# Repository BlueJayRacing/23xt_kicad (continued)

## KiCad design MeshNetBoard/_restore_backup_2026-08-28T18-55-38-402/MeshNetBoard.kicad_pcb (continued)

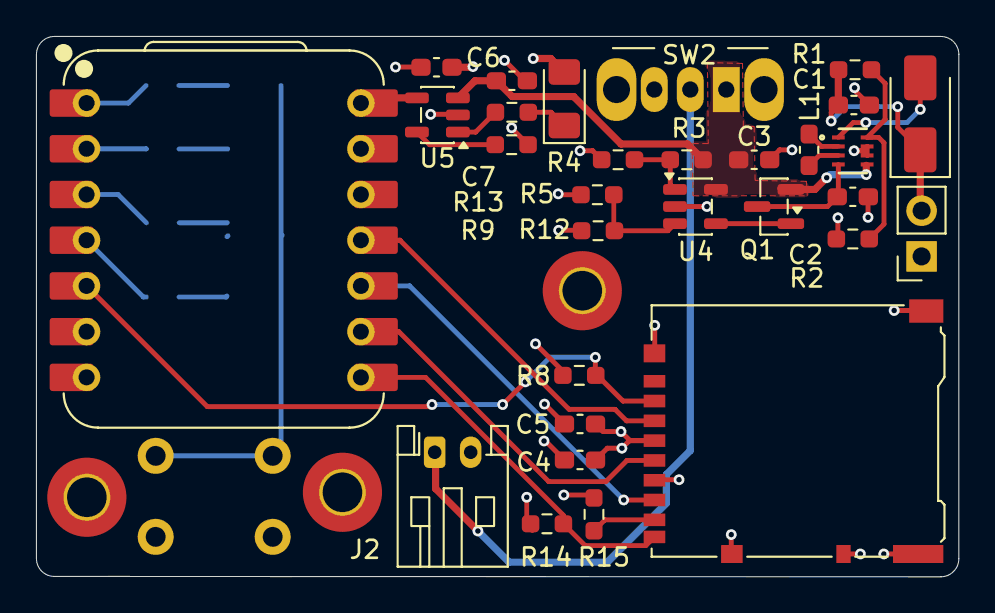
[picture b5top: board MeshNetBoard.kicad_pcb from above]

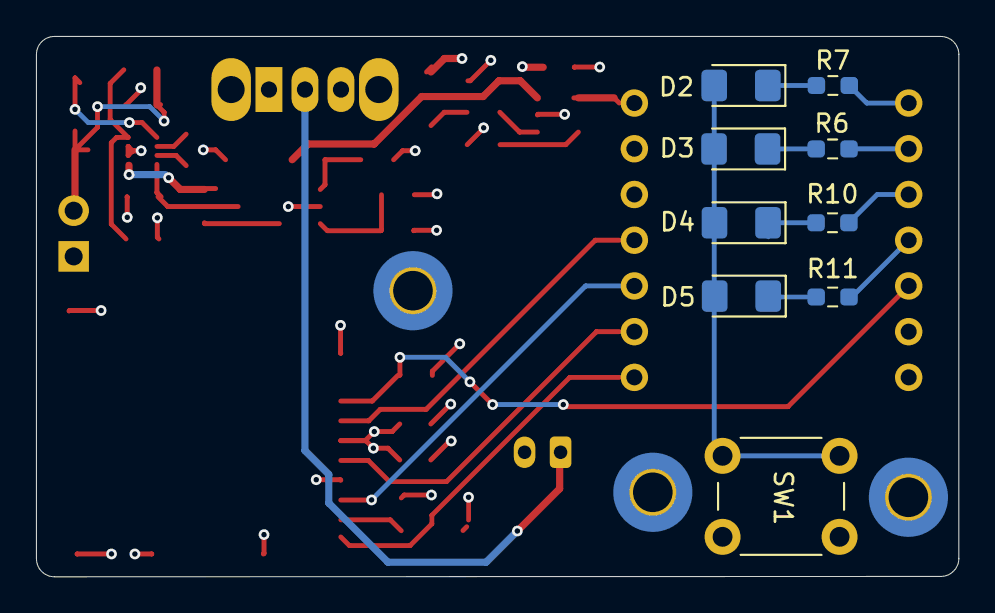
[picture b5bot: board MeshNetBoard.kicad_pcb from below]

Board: 4 copper layers, 51.2 x 30.0 mm, 42 parts (9 on the bottom side), 32 nets.

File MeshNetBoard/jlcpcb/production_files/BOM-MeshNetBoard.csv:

Comment,Designator,Footprint,LCSC,Quantity
0.1μF,C3,C_0603_1608Metric_Pad1.08x0.95mm_HandSolder,C125205,1
1.74M,R3,R_0603_1608Metric_Pad0.98x0.95mm_HandSolder,C422975,1
100nF,C4,C_0603_1608Metric_Pad1.08x0.95mm_HandSolder,C14663,1
10k,"R14,R15,R8",R_0603_1608Metric_Pad0.98x0.95mm_HandSolder,C23192,3
10µF,C5,C_0603_1608Metric_Pad1.08x0.95mm_HandSolder,C19702,1
1M,"R12,R4",R_0603_1608Metric_Pad0.98x0.95mm_HandSolder,C22935,2
1µH,L1,L_0603_1608Metric_Pad1.05x0.95mm_HandSolder,C98326,1
22µF,C2,C_0603_1608Metric_Pad1.08x0.95mm_HandSolder,C59461,1
2M,R5,R_0603_1608Metric_Pad0.98x0.95mm_HandSolder,C22976,1
2k,R9,R_0603_1608Metric_Pad0.98x0.95mm_HandSolder,C22975,1
330,"R10,R11,R6,R7",R_0603_1608Metric_Pad0.98x0.95mm_HandSolder,C23138,4
4.7µF,"C6,C7",C_0603_1608Metric_Pad1.08x0.95mm_HandSolder,C19666,2
470,R13,R_0603_1608Metric_Pad0.98x0.95mm_HandSolder,C23179,1
47µF,C1,C_0603_1608Metric_Pad1.08x0.95mm_HandSolder,C140782,1
511k,R1,R_0603_1608Metric_Pad0.98x0.95mm_HandSolder,C23194,1
91k,R2,R_0603_1608Metric_Pad0.98x0.95mm_HandSolder,C23265,1
Conn_01x02,J2,JST_PH_S2B-PH-K_1x02_P2.00mm_Horizontal,C173752,1
Jumper_2_Open,JP1,PinSocket_1x02_P2.54mm_Vertical,C6823945,1
LED,"D2,D3,D4,D5,D6",LED_1206_3216Metric_Pad1.42x1.75mm_HandSolder,C2827254,5
MAX9031AU,U4,SOT-23-5,C117531,1
MCP73831-2-OT,U5,SOT-23-5,C424093,1
Micro_SD_Card_Det_Hirose_DM3AT,J3,microSD_HC_Hirose_DM3AT-SF-PEJM5,C114218,1
Q_PMOS_GSD,Q1,SOT-23,C10487,1
SS14,D1,D_SMA,C2480,1
SW_Push,SW1,SW_PUSH_6mm_H5mm,C428628,1
SW_SPST,SW2,SW_Slide_SPDT_Angled_CK_OS102011MA1Q,C19192981,1
TPS631000DRLR,U2,TPS631000DRLR_TEX,C5219190,1
XIAO-ESP32-S3-DIP,U1,XIAO-ESP32-S3-DIP,C48405120,1

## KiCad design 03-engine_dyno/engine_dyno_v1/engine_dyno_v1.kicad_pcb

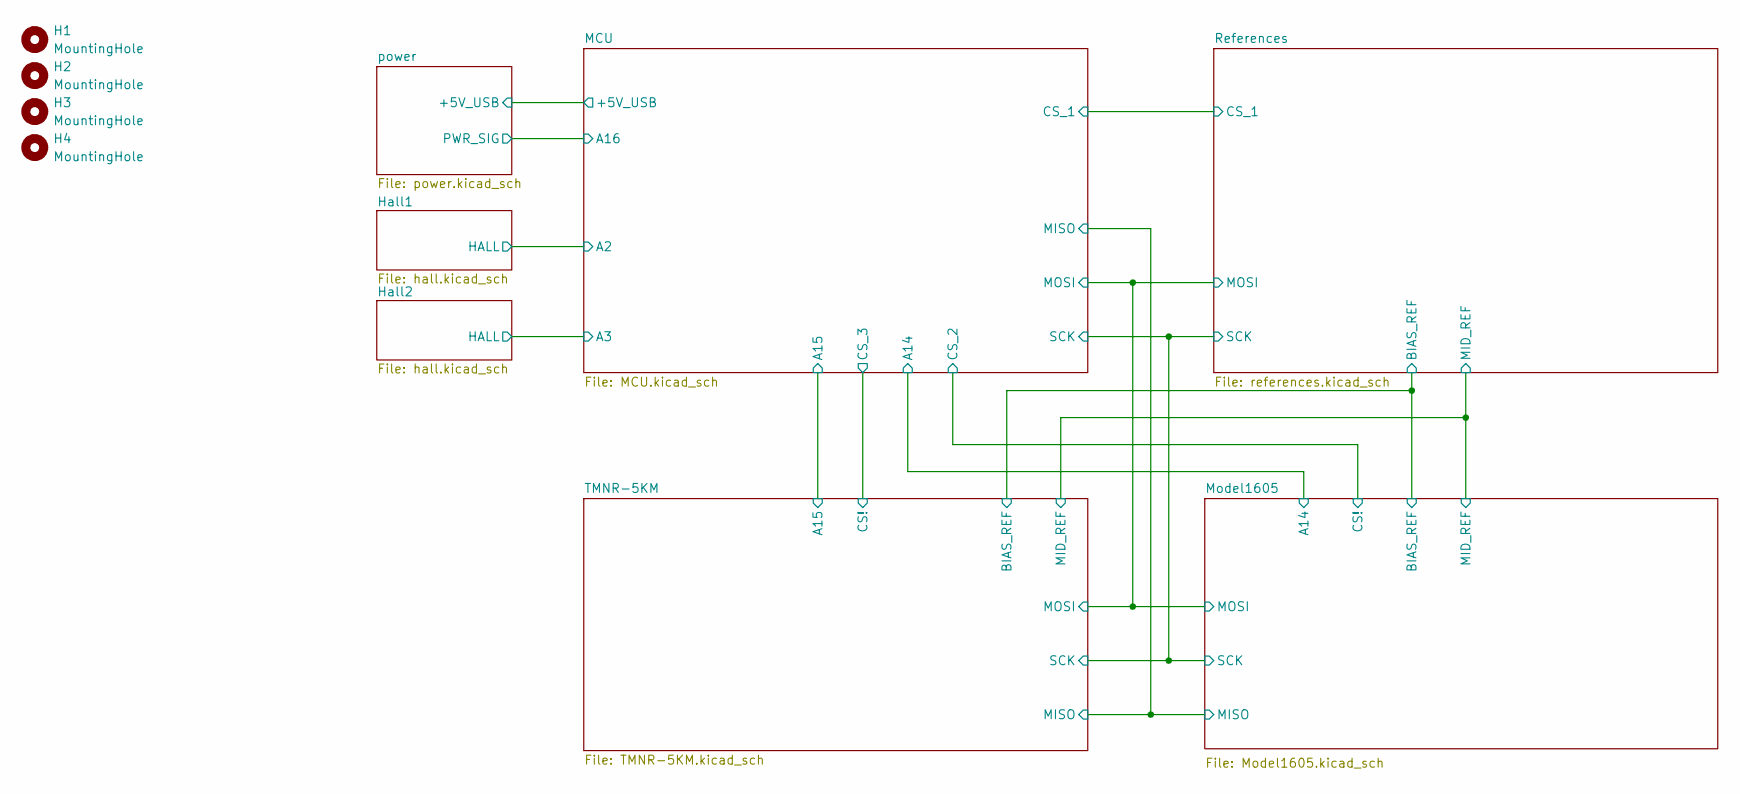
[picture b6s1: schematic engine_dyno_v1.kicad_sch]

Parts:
H1, H2, H3, H4: MountingHole; MountingHole_3.2mm_M3_DIN965_Pad

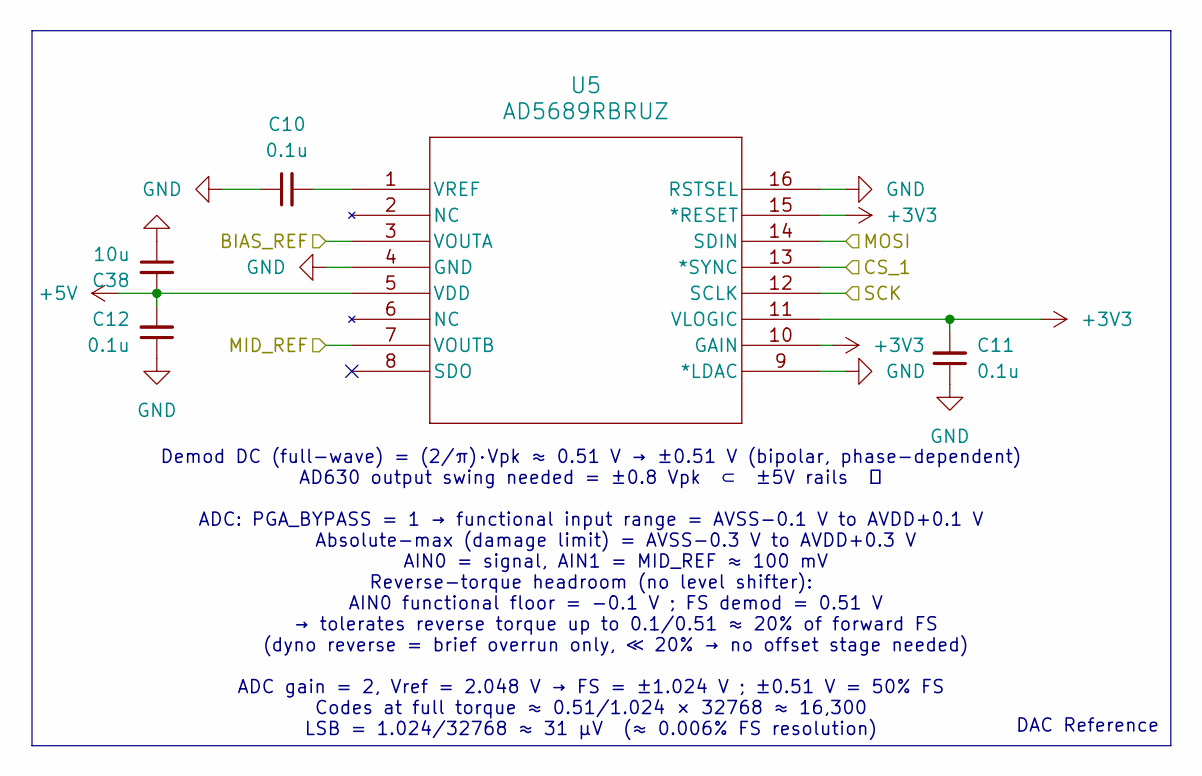
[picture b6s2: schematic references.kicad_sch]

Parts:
C10, C11, C12: 0.1u; C_0402_1005Metric
C38: 10u; C_0402_1005Metric
U5: AD5689RBRUZ; RU_16_ADI

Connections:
+3V3: C11.2, U5.10 (GAIN), U5.11 (VLOGIC), U5.15 (*RESET); also elsewhere on the board
+5V: C12.2, C38.2, U5.5 (VDD); also elsewhere on the board
/MCU/CS_1: U5.13 (*SYNC); also elsewhere on the board
/MCU/MOSI: U5.14 (SDIN); also elsewhere on the board
/MCU/SCK: U5.12 (SCLK); also elsewhere on the board
/Model1605/BIAS_REF: U5.3 (VOUTA); also elsewhere on the board
/Model1605/MID_REF: U5.7 (VOUTB); also elsewhere on the board
GND: C10.1, C11.1, C12.1, C38.1, U5.4 (GND), U5.9 (*LDAC), U5.16 (RSTSEL); also elsewhere on the board
unnamed: C10.2, U5.1 (VREF)

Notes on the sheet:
Demod DC (full-wave) = (2/π)·Vpk ≈ 0.51 V → ±0.51 V (bipolar, phase-dependent) AD630 output swing needed = ±0.8 Vpk ⊂ ±5V rails ✓ ADC: PGA_BYPASS = 1 → functional input range = AVSS−0.1 V to AVDD+0.1 V Absolute-max (damage limit) = AVSS−0.3 V to AVDD+0.3 V AIN0 = signal, AIN1 = MID_REF ≈ 100 mV Rev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
DAC Reference

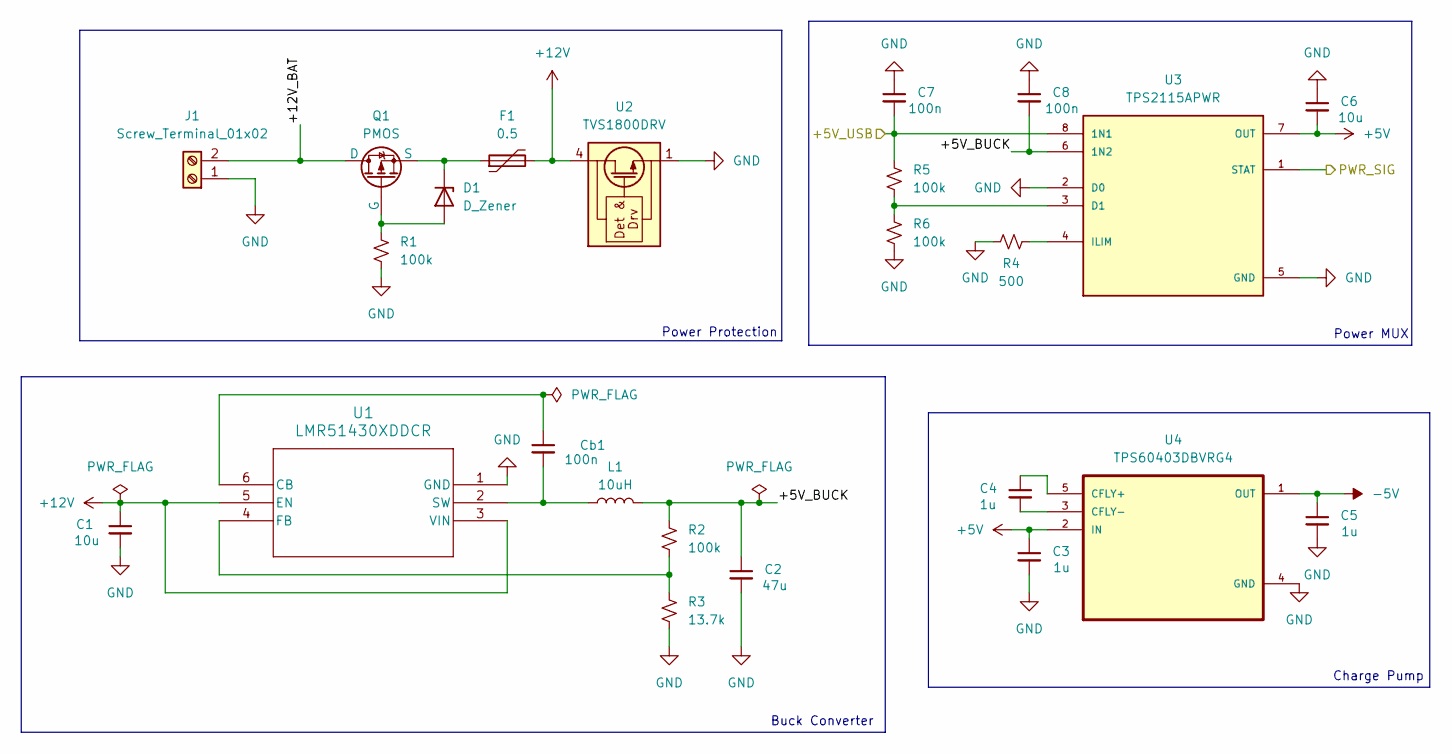
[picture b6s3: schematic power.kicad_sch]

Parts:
C1, C6: 10u; C_0402_1005Metric
C2: 47u; C_0402_1005Metric
C3, C4, C5: 1u; C_0402_1005Metric
C7, C8: 100n; C_0402_1005Metric
Cb1: 100n; C_0402_1005Metric
D1: D_Zener; D_SOD-123F
F1: 0.5; 0ZCH0050FF2G
J1: Screw_Terminal_01x02; TerminalBlock_RND_205-00232_1x02_P5.08mm_Horizontal
L1: 10uH; WE-MAPI_3020; MPN 74438336100
Q1: PMOS; SOT-23-3
R1, R2, R5, R6: 100k; R_0402_1005Metric
R3: 13.7k; R_0402_1005Metric
R4: 500; R_0402_1005Metric
U1: LMR51430XDDCR; SOT-23-THIN-6_DDC_TEX
U2: TVS1800DRV; WSON-6-1EP_2x2mm_P0.65mm_EP1x1.6mm
U3: TPS2115APWR; SOP65P640X120-8N; PARTREV F
U4: TPS60403DBVRG4; SOT95P280X145-5N

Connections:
+5V: C3.1, C6.2, U3.7 (OUT), U4.2 (IN); also elsewhere on the board
+12V: C1.1, F1.2, U1.3 (VIN), U1.5 (EN), U2.4 (IN), U2.5 (IN), U2.6 (IN)
-5V: C5.1, U4.1 (OUT); also elsewhere on the board
/MCU/+5V_USB: C7.2, R5.2, U3.8 (1N1); also elsewhere on the board
/MCU/A16: U3.1 (STAT); also elsewhere on the board
/power/+5V_BUCK: C2.1, C8.2, L1.2, R2.1, U3.6 (1N2)
/power/+12V_BAT: J1.2, Q1.1 (D)
GND: C1.2, C2.2, C3.2, C5.2, C6.1, C7.1, C8.1, J1.1, R1.2, R3.2, R4.2, R6.1, U1.1 (GND), U2.1 (GND), U2.2 (GND), U2.3 (GND), U2.7 (GND), U3.2 (D0), U3.5 (GND), U4.4 (GND); also elsewhere on the board
unnamed: D1.2 (A), Q1.2 (G), R1.1
unnamed: D1.1 (K), F1.1, Q1.3 (S)
unnamed: Cb1.1, U1.6 (CB)
unnamed: R2.2, R3.1, U1.4 (FB)
unnamed: Cb1.2, L1.1, U1.2 (SW)
unnamed: R5.1, R6.2, U3.3 (D1)
unnamed: R4.1, U3.4 (ILIM)
unnamed: C4.1, U4.5 (CFLY+)
unnamed: C4.2, U4.3 (CFLY-)

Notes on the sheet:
Power MUX
Charge Pump
Buck Converter
Power Protection

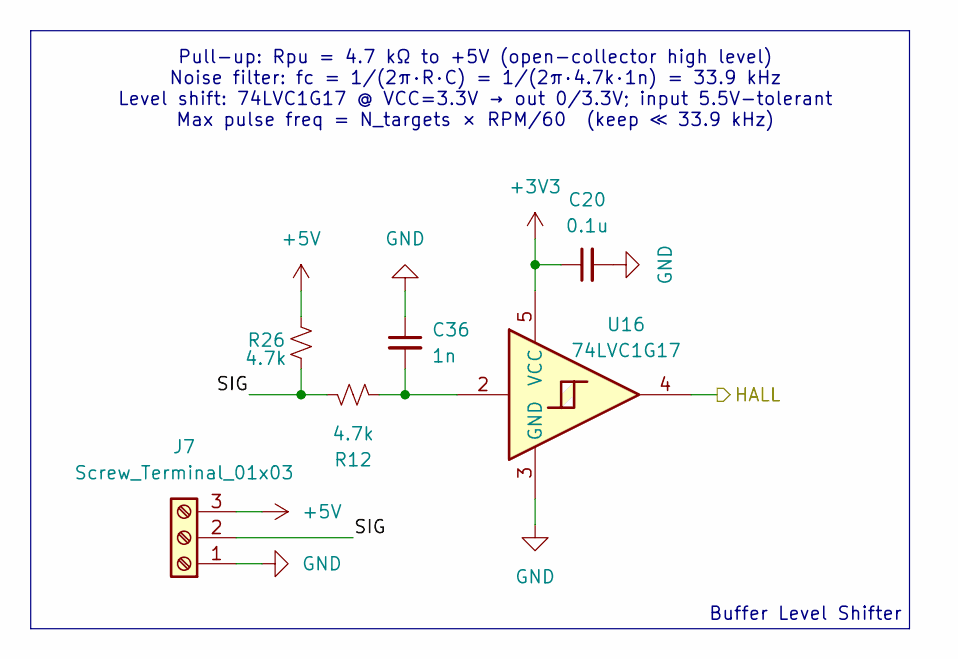
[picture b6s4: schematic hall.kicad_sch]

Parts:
C20: 0.1u; C_0402_1005Metric
C36: 1n; C_0402_1005Metric
J7: Screw_Terminal_01x03; TerminalBlock_RND_205-00233_1x03_P5.08mm_Horizontal
R12, R26: 4.7k; R_0402_1005Metric
U16: 74LVC1G17; SOT-23-5

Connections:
+3V3: C20.1, U16.5 (VCC); also elsewhere on the board
+5V: J7.3, R26.1; also elsewhere on the board
/Hall1/HALL: U16.4; also elsewhere on the board
/Hall1/SIG: J7.2, R12.1, R26.2
GND: C20.2, C36.1, J7.1, U16.3 (GND); also elsewhere on the board
unnamed: C36.2, R12.2, U16.2

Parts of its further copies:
C25: 0.1u; C_0402_1005Metric
C26: 1n; C_0402_1005Metric
J5: Screw_Terminal_01x03; TerminalBlock_RND_205-00233_1x03_P5.08mm_Horizontal
R17, R18: 4.7k; R_0402_1005Metric
U11: 74LVC1G17; SOT-23-5

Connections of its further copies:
+3V3: C25.1, U11.5 (VCC); also elsewhere on the board
+5V: J5.3, R17.1; also elsewhere on the board
/Hall2/HALL: U11.4; also elsewhere on the board
/Hall2/SIG: J5.2, R17.2, R18.1
GND: C25.2, C26.1, J5.1, U11.3 (GND); also elsewhere on the board
unnamed: C26.2, R18.2, U11.2

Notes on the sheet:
Pull-up: Rpu = 4.7 kΩ to +5V (open-collector high level) Noise filter: fc = 1/(2π·R·C) = 1/(2π·4.7k·1n) = 33.9 kHz Level shift: 74LVC1G17 @ VCC=3.3V → out 0/3.3V; input 5.5V-tolerant Max pulse freq = N_targets × RPM/60 (keep ≪ 33.9 kHz)
Buffer Level Shifter

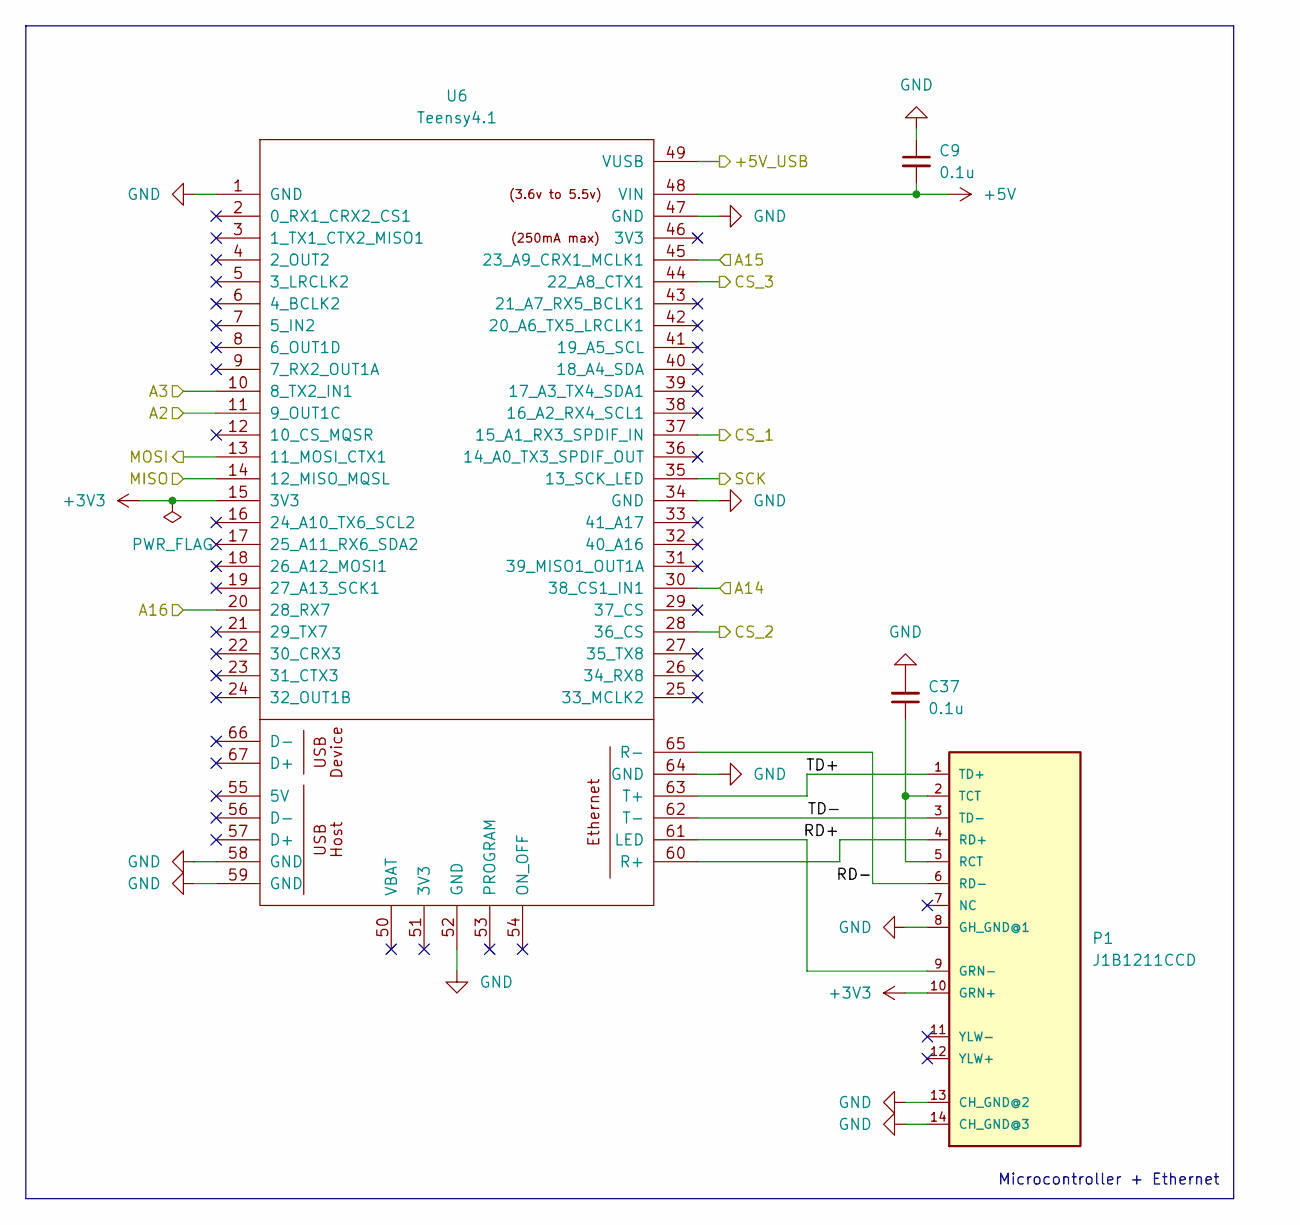
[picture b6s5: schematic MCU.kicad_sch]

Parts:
C9, C37: 0.1u; C_0402_1005Metric
P1: J1B1211CCD
U6: Teensy4.1; Teensy41

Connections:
+3V3: P1.10 (GRN+), U6.15 (3V3); also elsewhere on the board
+5V: C9.2, U6.48 (VIN); also elsewhere on the board
/Hall1/HALL: U6.11 (9_OUT1C); also elsewhere on the board
/Hall2/HALL: U6.10 (8_TX2_IN1); also elsewhere on the board
/MCU/+5V_USB: U6.49 (VUSB); also elsewhere on the board
/MCU/A14: U6.30 (38_CS1_IN1); also elsewhere on the board
/MCU/A15: U6.45 (23_A9_CRX1_MCLK1); also elsewhere on the board
/MCU/A16: U6.20 (28_RX7); also elsewhere on the board
/MCU/CS_1: U6.37 (15_A1_RX3_SPDIF_IN); also elsewhere on the board
/MCU/CS_2: U6.28 (36_CS); also elsewhere on the board
/MCU/CS_3: U6.44 (22_A8_CTX1); also elsewhere on the board
/MCU/MISO: U6.14 (12_MISO_MQSL); also elsewhere on the board
/MCU/MOSI: U6.13 (11_MOSI_CTX1); also elsewhere on the board
/MCU/RD+: P1.4 (RD+), U6.60 (R+)
/MCU/RD-: P1.6 (RD-), U6.65 (R-)
/MCU/SCK: U6.35 (13_SCK_LED); also elsewhere on the board
/MCU/TD+: P1.1 (TD+), U6.63 (T+)
/MCU/TD-: P1.3 (TD-), U6.62 (T-)
GND: C9.1, C37.2, P1.8 (GH_GND@1), P1.13 (CH_GND@2), P1.14 (CH_GND@3), U6.1 (GND), U6.34 (GND), U6.47 (GND), U6.52 (GND), U6.58 (GND), U6.59 (GND), U6.64 (GND); also elsewhere on the board
unnamed: P1.9 (GRN-), U6.61 (LED)
unnamed: C37.1, P1.2 (TCT), P1.5 (RCT)

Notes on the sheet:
Microcontroller + Ethernet

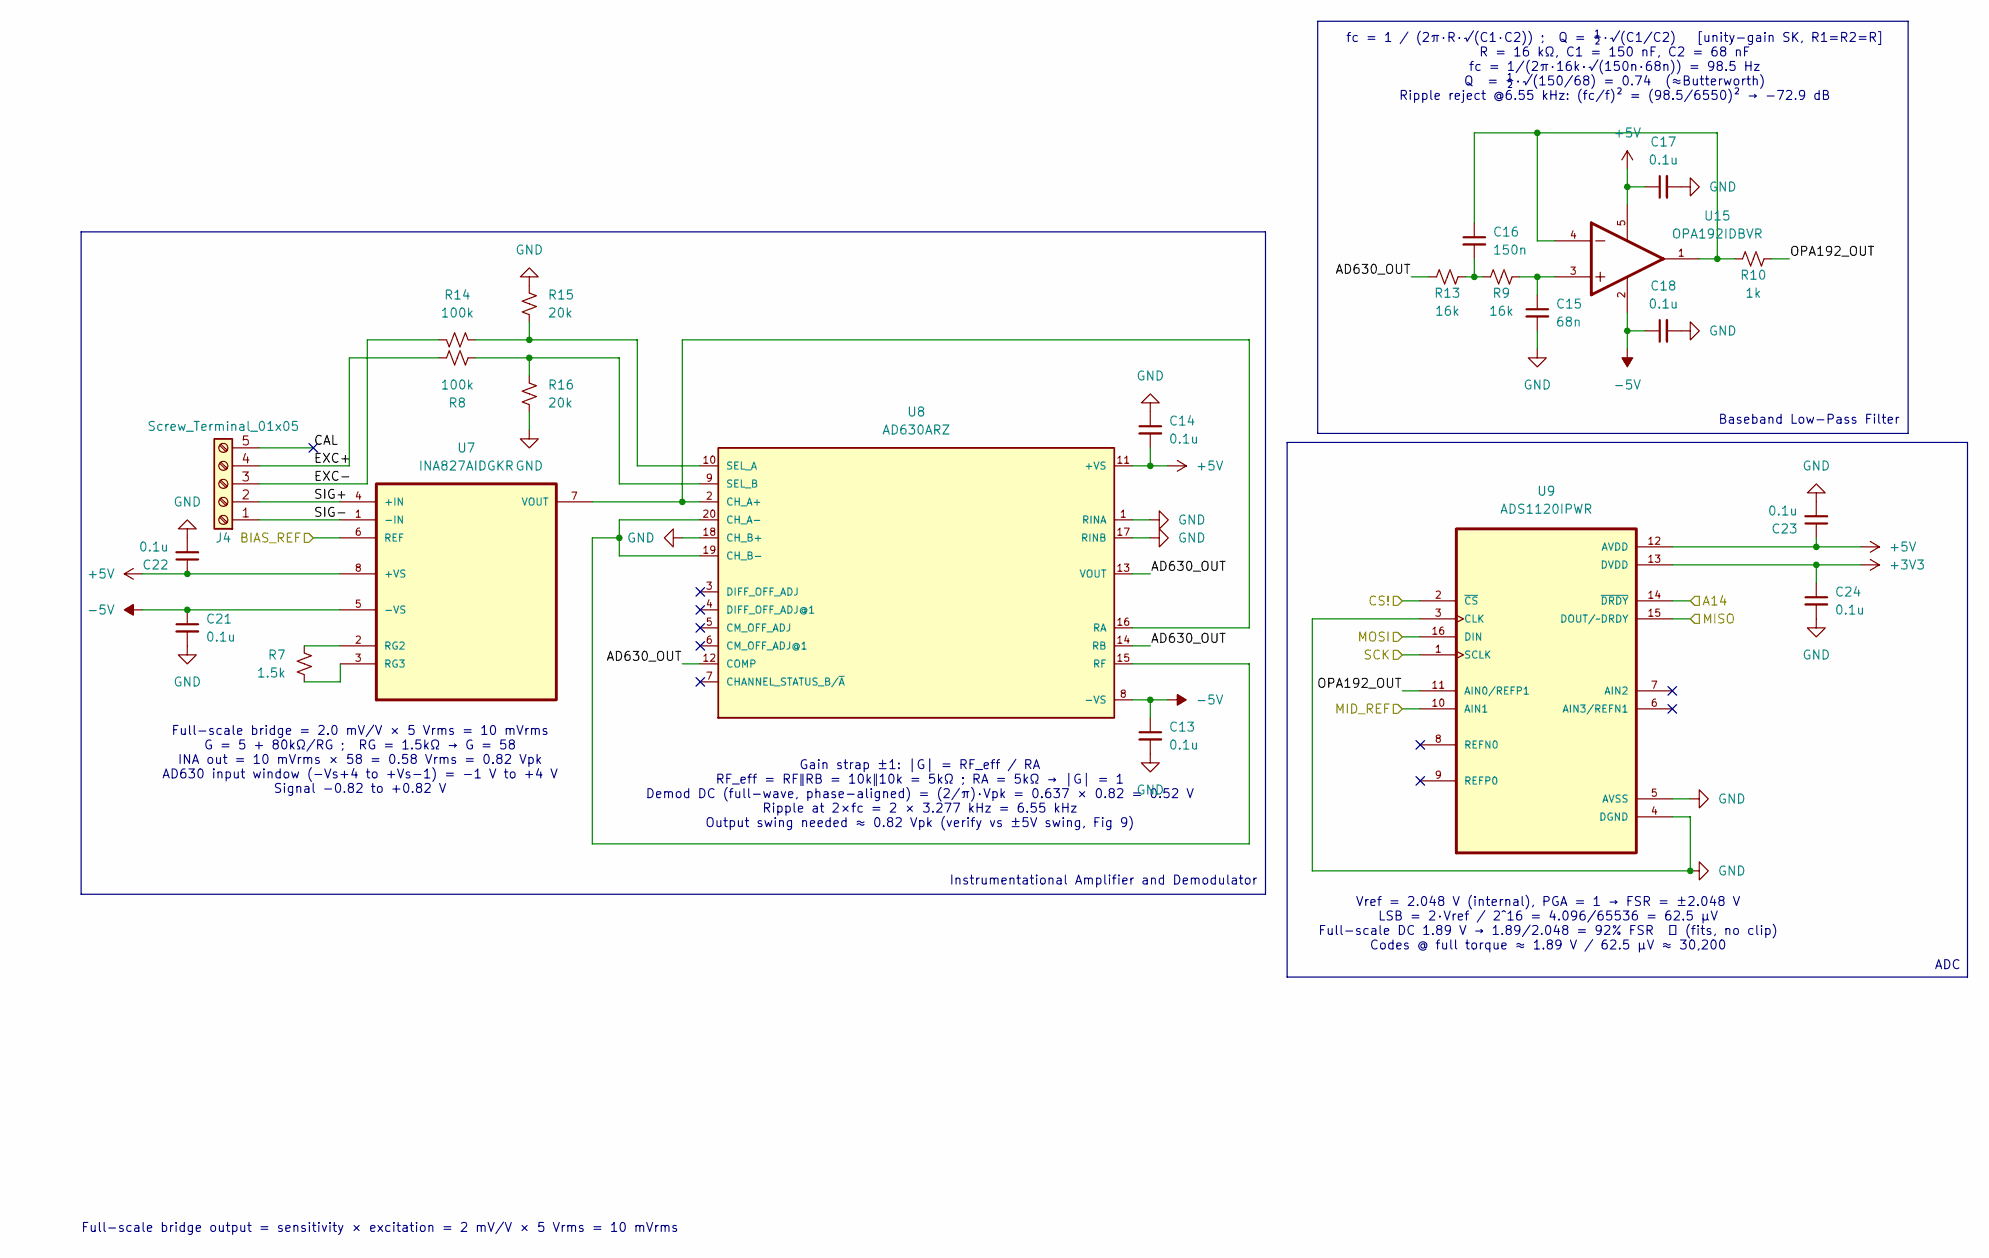
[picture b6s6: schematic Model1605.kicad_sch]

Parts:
C13, C14, C17, C18, C21, C22, C23, C24: 0.1u; C_0402_1005Metric
C15: 68n; C_0402_1005Metric
C16: 150n; C_0402_1005Metric
J4: Screw_Terminal_01x05; TerminalBlock_RND_205-00235_1x05_P5.08mm_Horizontal
R7: 1.5k; R_0402_1005Metric
R8, R14: 100k; R_0402_1005Metric
R9, R13: 16k; R_0402_1005Metric
R10: 1k; R_0402_1005Metric
R15, R16: 20k; R_0402_1005Metric
U7: INA827AIDGKR; SOP65P490X110-8N; DigiKey_Part_Number 296-30588-1-ND
U8: AD630ARZ; SOIC127P1032X265-20N
U9: ADS1120IPWR; SOP65P640X120-16N
U15: OPA192IDBVR; SOT95P280X145-5N; PARTREV F

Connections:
+3V3: C24.1, U9.13 (DVDD); also elsewhere on the board
+5V: C14.2, C17.1, C22.1, C23.1, U7.8 (+VS), U8.11 (+VS), U9.12 (AVDD), U15.5; also elsewhere on the board
-5V: C13.1, C18.1, C21.1, U7.5 (-VS), U8.8 (-VS), U15.2; also elsewhere on the board
/MCU/A14: U9.14 (~DRDY); also elsewhere on the board
/MCU/CS_2: U9.2 (~CS); also elsewhere on the board
/MCU/MISO: U9.15 (DOUT/~DRDY); also elsewhere on the board
/MCU/MOSI: U9.16 (DIN); also elsewhere on the board
/MCU/SCK: U9.1 (SCLK); also elsewhere on the board
/Model1605/AD630_OUT: R13.1, U8.12 (COMP), U8.13 (VOUT), U8.14 (RB)
/Model1605/BIAS_REF: U7.6 (REF); also elsewhere on the board
/Model1605/CAL: J4.5
/Model1605/EXC+: J4.4, R8.1
/Model1605/EXC-: J4.3, R14.1
/Model1605/MID_REF: U9.10 (AIN1); also elsewhere on the board
/Model1605/OPA192_OUT: R10.2, U9.11 (AIN0/REFP1)
/Model1605/SIG+: J4.2, U7.4 (+IN)
/Model1605/SIG-: J4.1, U7.1 (-IN)
GND: C13.2, C14.1, C15.2, C17.2, C18.2, C21.2, C22.2, C23.2, C24.2, R15.2, R16.1, U8.1 (RINA), U8.17 (RINB), U8.18 (CH_B+), U9.3 (CLK), U9.4 (DGND), U9.5 (AVSS); also elsewhere on the board
unnamed: C15.1, R9.2, U15.3
unnamed: C16.1, R10.1, U15.1, U15.4
unnamed: C16.2, R9.1, R13.2
unnamed: R7.1, U7.2 (RG2)
unnamed: R7.2, U7.3 (RG3)
unnamed: U7.7 (VOUT), U8.2 (CH_A+), U8.16 (RA)
unnamed: U8.15 (RF), U8.19 (CH_B-), U8.20 (CH_A-)
unnamed: R14.2, R15.1, U8.10 (SEL_A)
unnamed: R8.2, R16.2, U8.9 (SEL_B)

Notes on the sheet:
Baseband Low-Pass Filter
Vref = 2.048 V (internal), PGA = 1 → FSR = ±2.048 V LSB = 2·Vref / 2^16 = 4.096/65536 = 62.5 µV Full-scale DC 1.89 V → 1.89/2.048 = 92% FSR ✓ (fits, no clip) Codes @ full torque ≈ 1.89 V / 62.5 µV ≈ 30,200
Full-scale bridge = 2.0 mV/V × 5 Vrms = 10 mVrms G = 5 + 80kΩ/RG ; RG = 1.5kΩ → G = 58 INA out = 10 mVrms × 58 = 0.58 Vrms = 0.82 Vpk AD630 input window (−Vs+4 to +Vs−1) = −1 V to +4 V Signal −0.82 to +0.82 V
Full-scale bridge output = sensitivity × excitation = 2 mV/V × 5 Vrms = 10 mVrms
fc = 1 / (2π·R·√(C1·C2)) ; Q = ½·√(C1/C2) [unity-gain SK, R1=R2=R] R = 16 kΩ, C1 = 150 nF, C2 = 68 nF fc = 1/(2π·16k·√(150n·68n)) = 98.5 Hz Q = ½·√(150/68) = 0.74 (≈Butterworth) Ripple reject @6.55 kHz: (fc/f)² = (98.5/6550)² → −72.9 dB
Instrumentational Amplifier and Demodulator
ADC
Gain strap ±1: |G| = RF_eff / RA RF_eff = RF‖RB = 10k‖10k = 5kΩ ; RA = 5kΩ → |G| = 1 Demod DC (full-wave, phase-aligned) = (2/π)·Vpk = 0.637 × 0.82 = 0.52 V Ripple at 2×fc = 2 × 3.277 kHz = 6.55 kHz Output swing needed ≈ 0.82 Vpk (verify vs ±5V swing, Fig 9)

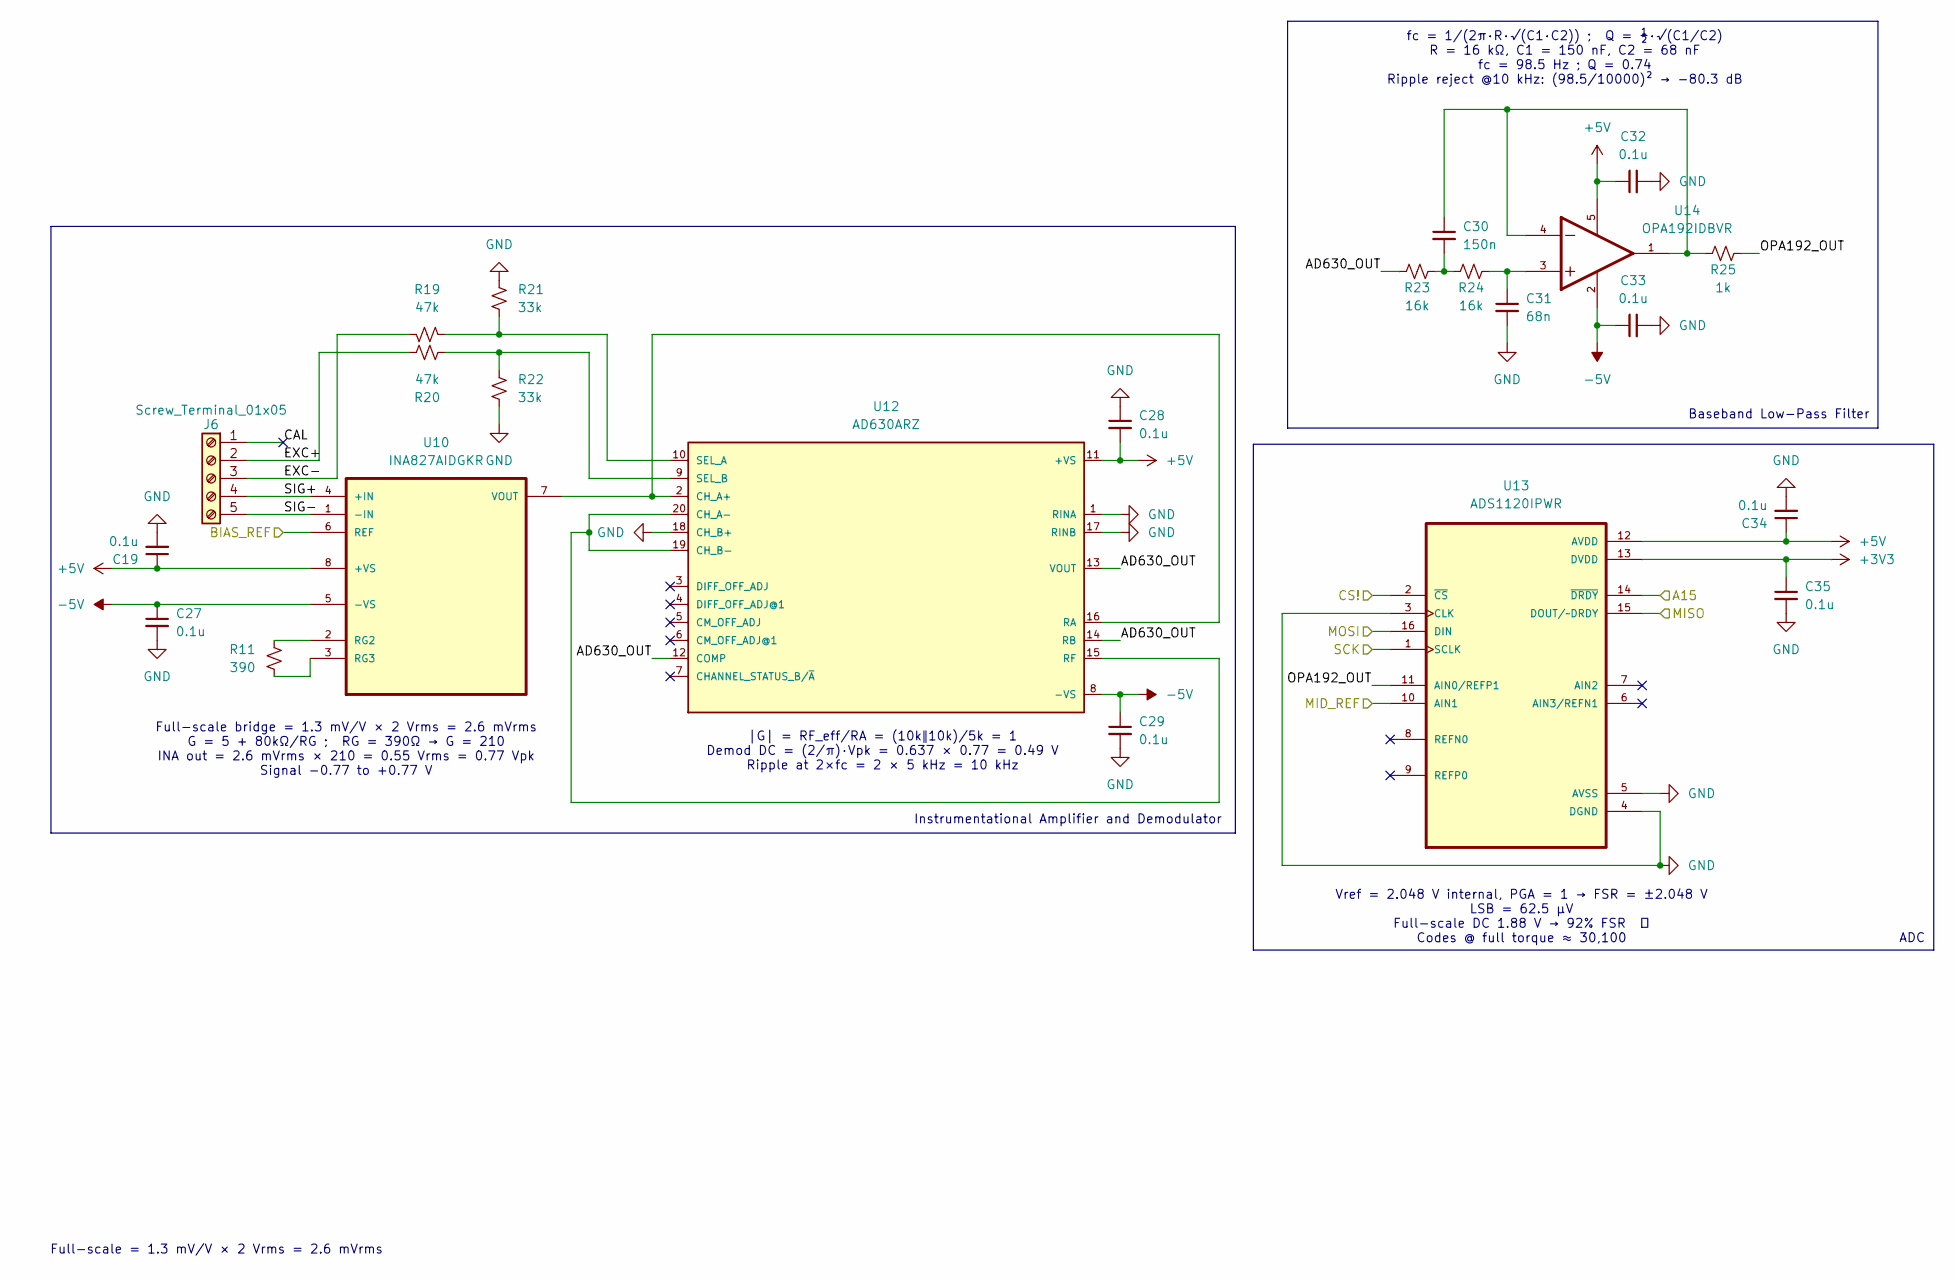
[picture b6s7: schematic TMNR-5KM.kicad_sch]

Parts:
C19, C27, C28, C29, C32, C33, C34, C35: 0.1u; C_0402_1005Metric
C30: 150n; C_0402_1005Metric
C31: 68n; C_0402_1005Metric
J6: Screw_Terminal_01x05; TerminalBlock_RND_205-00235_1x05_P5.08mm_Horizontal
R11: 390; R_0402_1005Metric
R19, R20: 47k; R_0402_1005Metric
R21, R22: 33k; R_0402_1005Metric
R23, R24: 16k; R_0402_1005Metric
R25: 1k; R_0402_1005Metric
U10: INA827AIDGKR; SOP65P490X110-8N; DigiKey_Part_Number 296-30588-1-ND
U12: AD630ARZ; SOIC127P1032X265-20N
U13: ADS1120IPWR; SOP65P640X120-16N
U14: OPA192IDBVR; SOT95P280X145-5N; PARTREV F

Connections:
+3V3: C35.1, U13.13 (DVDD); also elsewhere on the board
+5V: C19.1, C28.2, C32.1, C34.1, U10.8 (+VS), U12.11 (+VS), U13.12 (AVDD), U14.5; also elsewhere on the board
-5V: C27.1, C29.1, C33.1, U10.5 (-VS), U12.8 (-VS), U14.2; also elsewhere on the board
/MCU/A15: U13.14 (~DRDY); also elsewhere on the board
/MCU/CS_3: U13.2 (~CS); also elsewhere on the board
/MCU/MISO: U13.15 (DOUT/~DRDY); also elsewhere on the board
/MCU/MOSI: U13.16 (DIN); also elsewhere on the board
/MCU/SCK: U13.1 (SCLK); also elsewhere on the board
/Model1605/BIAS_REF: U10.6 (REF); also elsewhere on the board
/Model1605/MID_REF: U13.10 (AIN1); also elsewhere on the board
/TMNR-5KM/AD630_OUT: R23.1, U12.12 (COMP), U12.13 (VOUT), U12.14 (RB)
/TMNR-5KM/CAL: J6.1
/TMNR-5KM/EXC+: J6.2, R20.1
/TMNR-5KM/EXC-: J6.3, R19.1
/TMNR-5KM/OPA192_OUT: R25.2, U13.11 (AIN0/REFP1)
/TMNR-5KM/SIG+: J6.4, U10.4 (+IN)
/TMNR-5KM/SIG-: J6.5, U10.1 (-IN)
GND: C19.2, C27.2, C28.1, C29.2, C31.2, C32.2, C33.2, C34.2, C35.2, R21.2, R22.1, U12.1 (RINA), U12.17 (RINB), U12.18 (CH_B+), U13.3 (CLK), U13.4 (DGND), U13.5 (AVSS); also elsewhere on the board
unnamed: C30.1, R25.1, U14.1, U14.4
unnamed: C30.2, R23.2, R24.1
unnamed: C31.1, R24.2, U14.3
unnamed: R11.1, U10.2 (RG2)
unnamed: R11.2, U10.3 (RG3)
unnamed: U10.7 (VOUT), U12.2 (CH_A+), U12.16 (RA)
unnamed: U12.15 (RF), U12.19 (CH_B-), U12.20 (CH_A-)
unnamed: R19.2, R21.1, U12.10 (SEL_A)
unnamed: R20.2, R22.2, U12.9 (SEL_B)

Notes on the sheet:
Baseband Low-Pass Filter
fc = 1/(2π·R·√(C1·C2)) ; Q = ½·√(C1/C2) R = 16 kΩ, C1 = 150 nF, C2 = 68 nF fc = 98.5 Hz ; Q = 0.74 Ripple reject @10 kHz: (98.5/10000)² → −80.3 dB
Full-scale bridge = 1.3 mV/V × 2 Vrms = 2.6 mVrms G = 5 + 80kΩ/RG ; RG = 390Ω → G = 210 INA out = 2.6 mVrms × 210 = 0.55 Vrms = 0.77 Vpk Signal −0.77 to +0.77 V
Full-scale = 1.3 mV/V × 2 Vrms = 2.6 mVrms
Vref = 2.048 V internal, PGA = 1 → FSR = ±2.048 V LSB = 62.5 µV Full-scale DC 1.88 V → 92% FSR ✓ Codes @ full torque ≈ 30,100
|G| = RF_eff/RA = (10k‖10k)/5k = 1 Demod DC = (2/π)·Vpk = 0.637 × 0.77 = 0.49 V Ripple at 2×fc = 2 × 5 kHz = 10 kHz
Instrumentational Amplifier and Demodulator
ADC

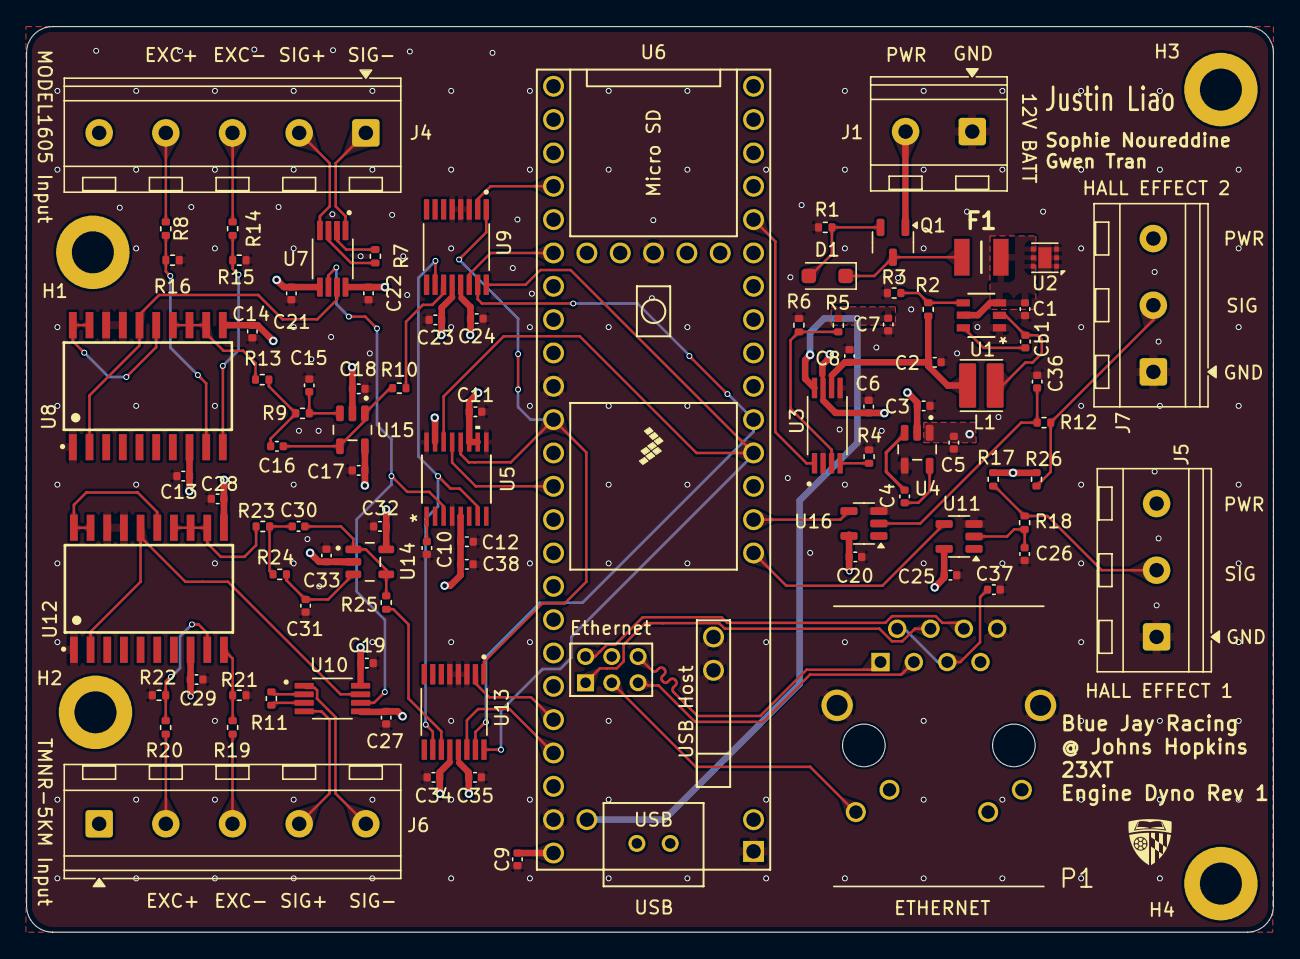
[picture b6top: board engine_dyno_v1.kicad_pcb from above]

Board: 4 copper layers, 95.0 x 69.0 mm, 95 parts (0 on the bottom side), 71 nets.

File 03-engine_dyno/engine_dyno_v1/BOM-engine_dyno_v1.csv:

Item # ,Designator,DNP,Qty,Manufacturer,LCSC,Mfg Part #,Description/Value,Package/Footprint,Type
1,"C1,C6,C38",,3,,,,"Ceramic capacitor, 10uF, 0402",0402 (1005 Metric),SMD
2,C2,,1,,,,"Ceramic capacitor, 47uF, 0402",0402 (1005 Metric),SMD
3,"C3,C4,C5",,3,,,,"Ceramic capacitor, 1uF, 0402",0402 (1005 Metric),SMD
4,"C7,C8,Cb1,C9,C10,C11,C12,C13,C14,C17,C18,C19,C20,C21,C22,C23,C24,C25,C27,C28,C29,C32,C33,C34,C35,C37",,26,,,,"Ceramic capacitor, 100nF, 0402",0402 (1005 Metric),SMD
5,"C15,C31",,2,,,,"Ceramic capacitor, 68nF, 0402",0402 (1005 Metric),SMD
6,"C16,C30",,2,,,,"Ceramic capacitor, 150nF, 0402",0402 (1005 Metric),SMD
7,"C26,C36",,2,,,,"Ceramic capacitor, 1nF, 0402",0402 (1005 Metric),SMD
8,"R1,R2,R5,R6,R8,R14",,6,,,,"Chip resistor, 100kΩ, 0402",0402 (1005 Metric),SMD
9,R3,,1,,,,"Chip resistor, 13.7kΩ, 0402",0402 (1005 Metric),SMD
10,R4,,1,,,,"Chip resistor, 500Ω, 0402",0402 (1005 Metric),SMD
11,R7,,1,,,,"Chip resistor, 1.5kΩ, 0402",0402 (1005 Metric),SMD
12,"R9,R13,R23,R24",,4,,,,"Chip resistor, 16kΩ, 0402",0402 (1005 Metric),SMD
13,"R10,R25",,2,,,,"Chip resistor, 1kΩ, 0402",0402 (1005 Metric),SMD
14,R11,,1,,,,"Chip resistor, 390Ω, 0402",0402 (1005 Metric),SMD
15,"R12,R17,R18,R26",,4,,,,"Chip resistor, 4.7kΩ, 0402",0402 (1005 Metric),SMD
16,"R15,R16",,2,,,,"Chip resistor, 20kΩ, 0402",0402 (1005 Metric),SMD
17,"R19,R20",,2,,,,"Chip resistor, 47kΩ, 0402",0402 (1005 Metric),SMD
18,"R21,R22",,2,,,,"Chip resistor, 33kΩ, 0402",0402 (1005 Metric),SMD
19,L1,,1,Würth Elektronik,,74438336100,3.0 × 3.0 × 2.0 mm power inductor; IRP 1.65A; Isat 1.55A at 10% / 3.0A at 30%.,WE-MAPI 3020,SMD
